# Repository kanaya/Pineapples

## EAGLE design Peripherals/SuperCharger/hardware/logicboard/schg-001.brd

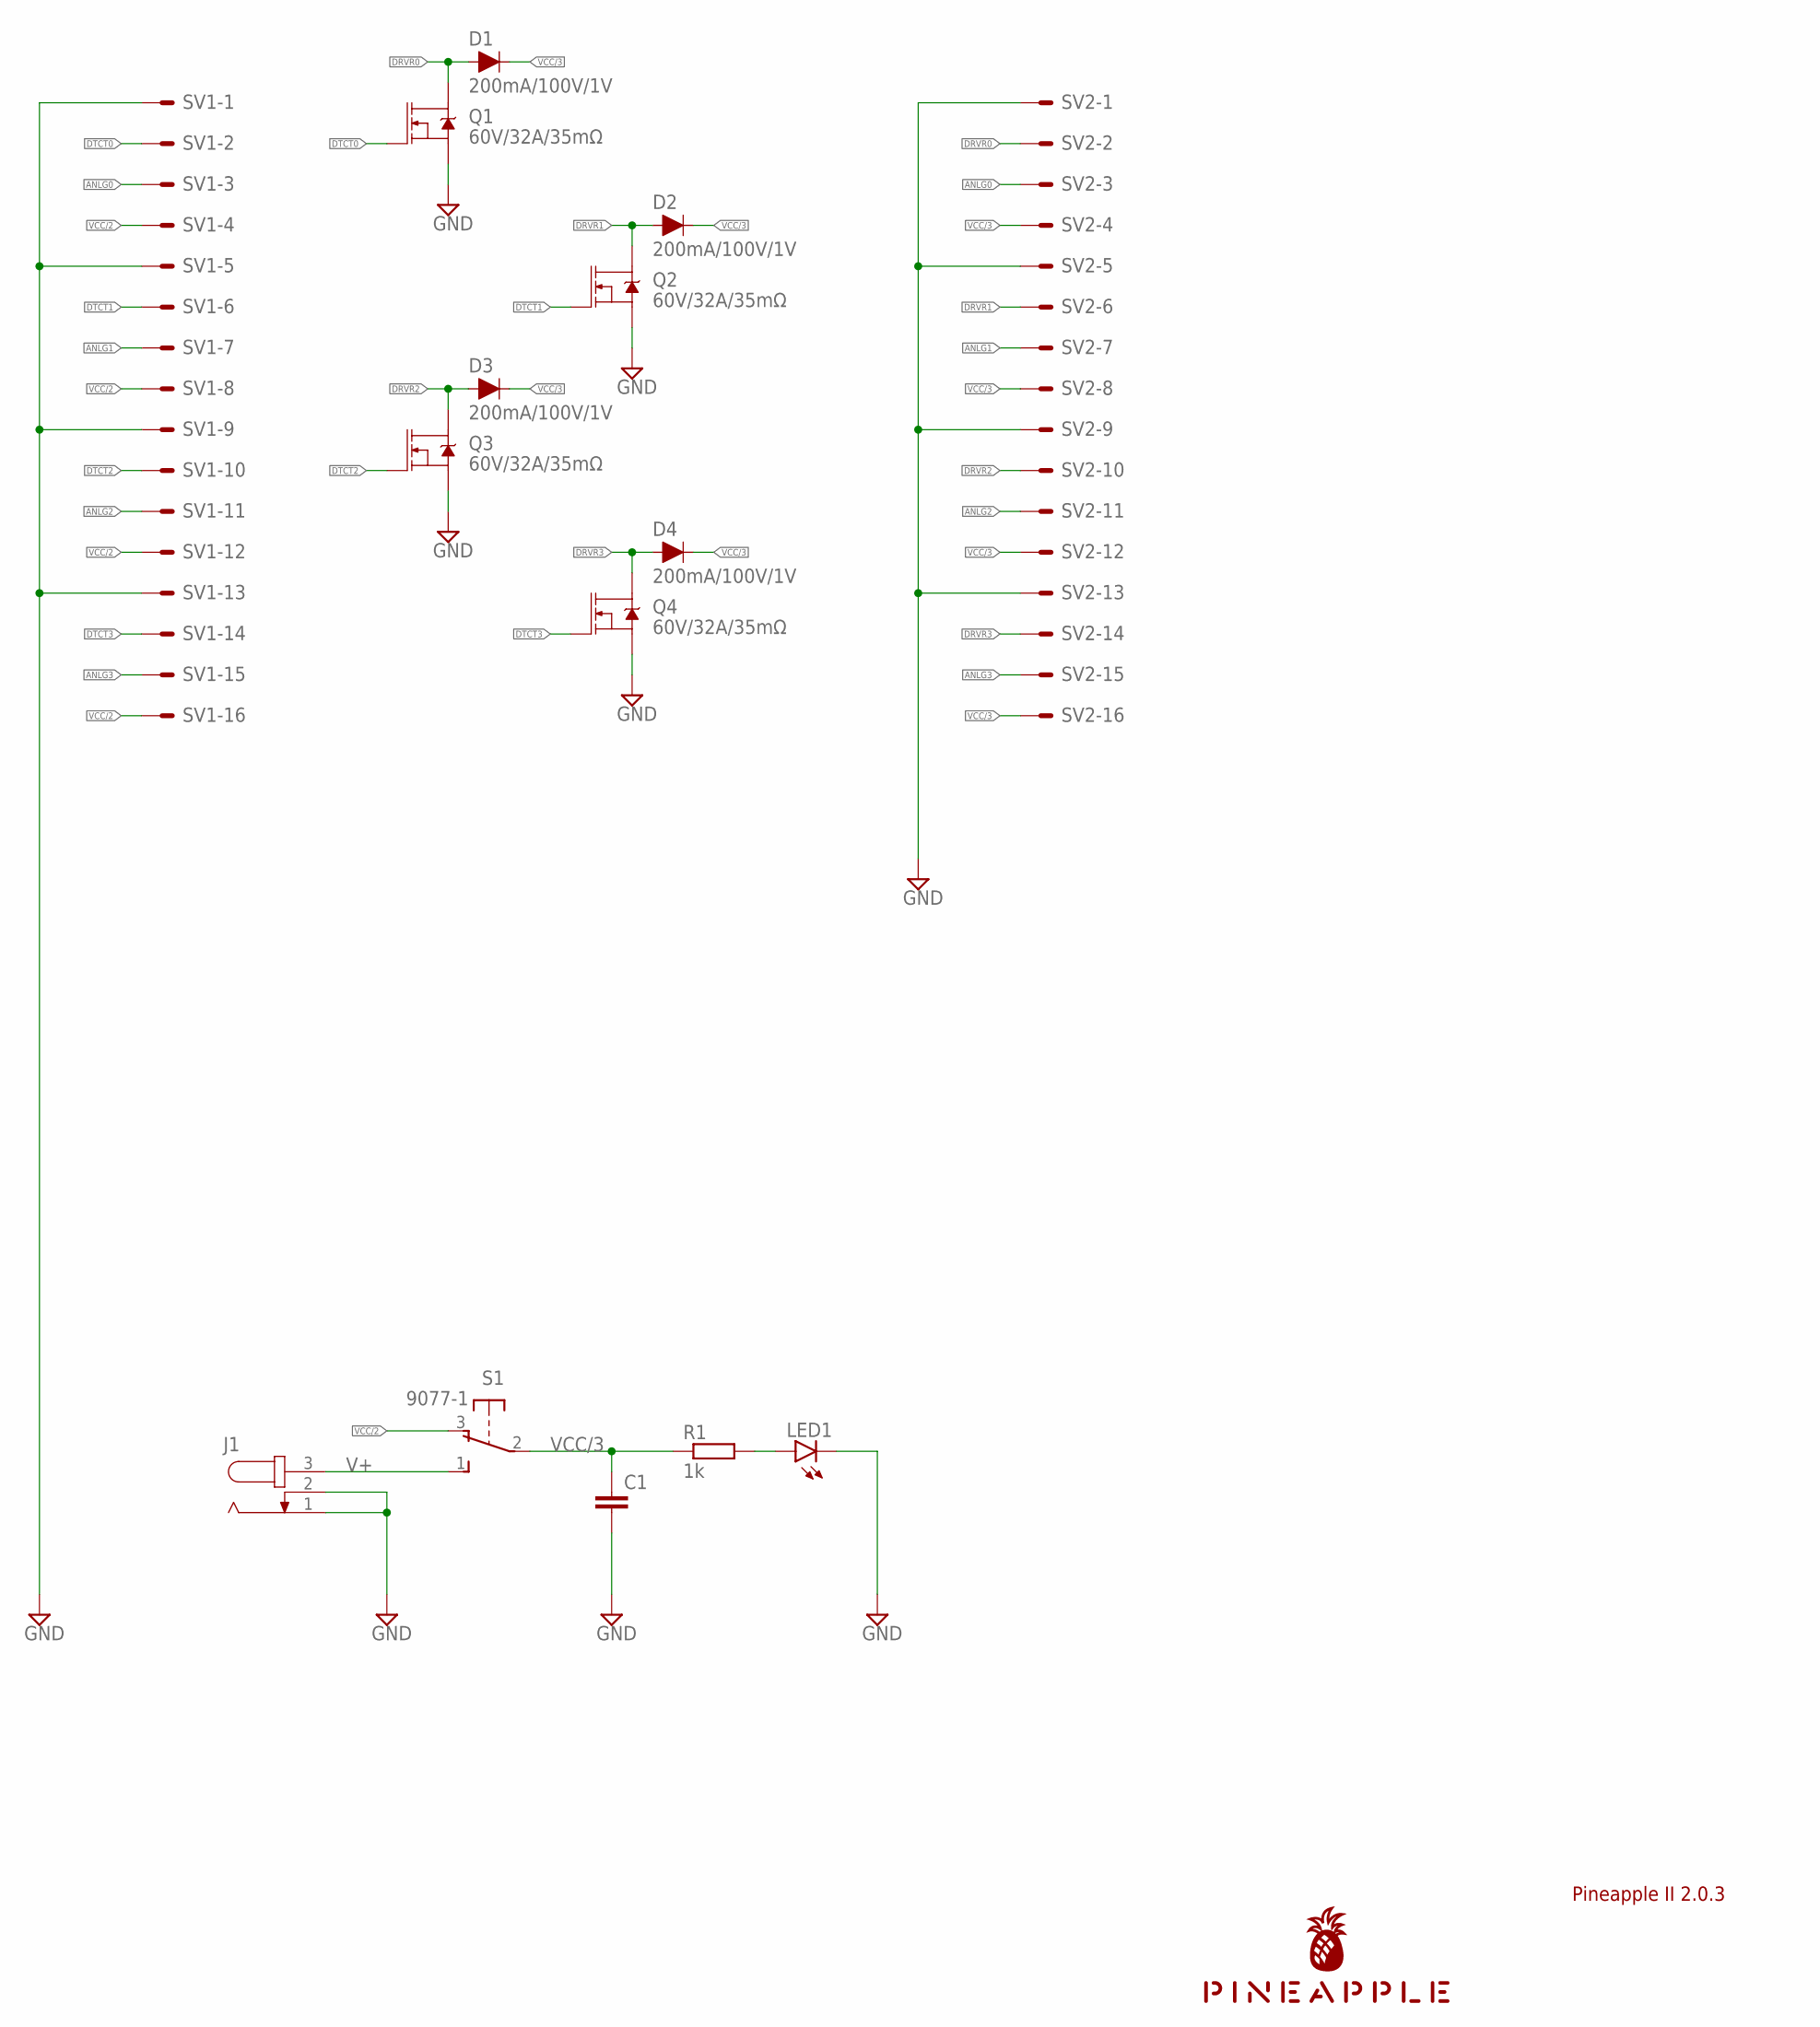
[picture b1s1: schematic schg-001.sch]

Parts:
C1: C-EU025-025X050; C025-025X050
D1, D2, D3, D4: 200mA/100V/1V; DIODE-1N4148
J1: JACK-PLUG0; SPC4077
LED1: LED3MM
Q1, Q2, Q3, Q4: 60V/32A/35mΩ; TO220V
R1: 1k; 0204/5
S1: 9077-1
SV1, SV2: ML16LE; ML16L
U$1: PINEAPPLE450_SILK

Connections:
ANLG0: SV1.3, SV2.3
ANLG1: SV1.7, SV2.7
ANLG2: SV1.11, SV2.11
ANLG3: SV1.15, SV2.15
DRVR0: D1.A, Q1.2 (D), SV2.2
DRVR1: D2.A, Q2.2 (D), SV2.6
DRVR2: D3.A, Q3.2 (D), SV2.10
DRVR3: D4.A, Q4.2 (D), SV2.14
DTCT0: Q1.1 (G), SV1.2
DTCT1: Q2.1 (G), SV1.6
DTCT2: Q3.1 (G), SV1.10
DTCT3: Q4.1 (G), SV1.14
GND: C1.2, J1.1, J1.2, LED1.K (C), Q1.3 (S), Q2.3 (S), Q3.3 (S), Q4.3 (S), SV1.1, SV1.5, SV1.9, SV1.13, SV2.1, SV2.5, SV2.9, SV2.13
V+: J1.3, S1.1 (S)
VCC2LED: LED1.A, R1.2
VCC/2: S1.3 (O), SV1.4, SV1.8, SV1.12, SV1.16
VCC/3: C1.1, D1.C, D2.C, D3.C, D4.C, R1.1, S1.2, SV2.4, SV2.8, SV2.12, SV2.16

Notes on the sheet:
Pineapple II 2.0.3

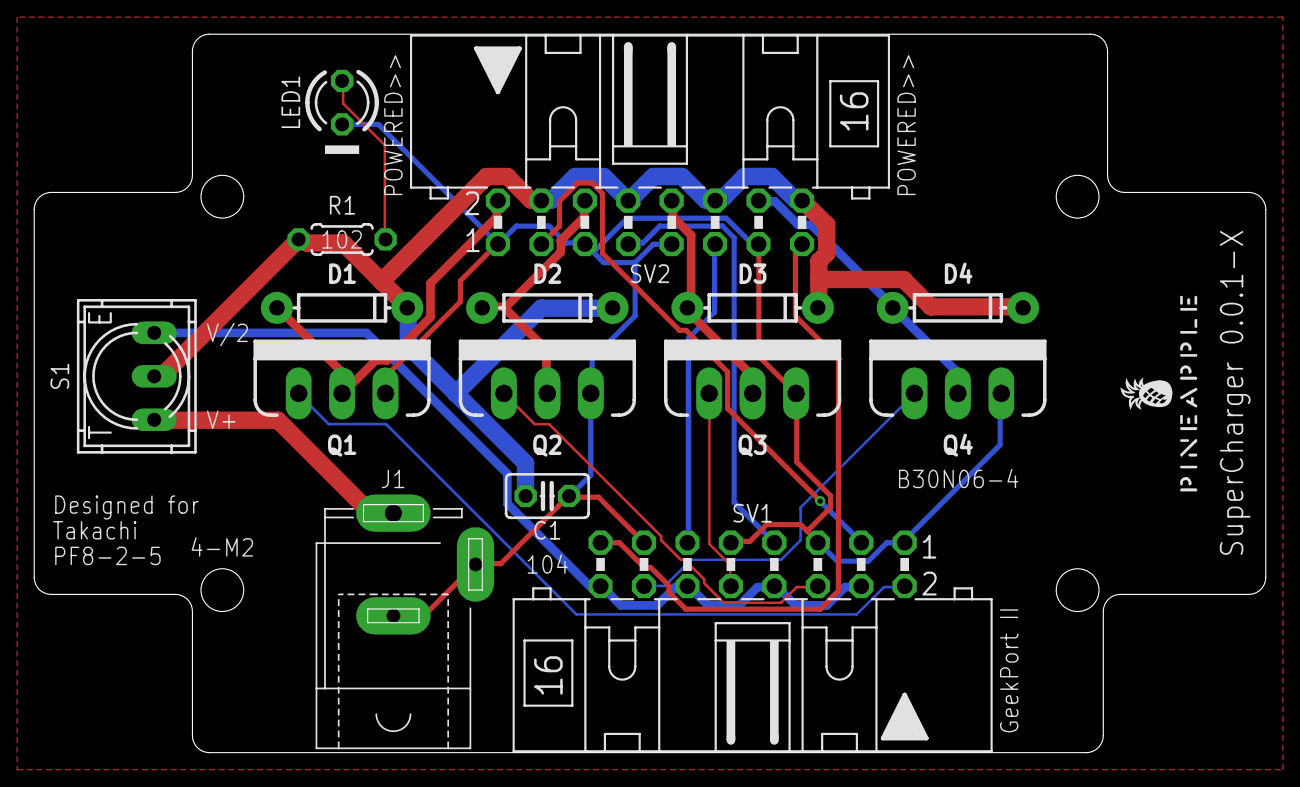
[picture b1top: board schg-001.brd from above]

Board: 2 copper layers, 72.0 x 42.0 mm, 16 parts (0 on the bottom side), 17 nets.

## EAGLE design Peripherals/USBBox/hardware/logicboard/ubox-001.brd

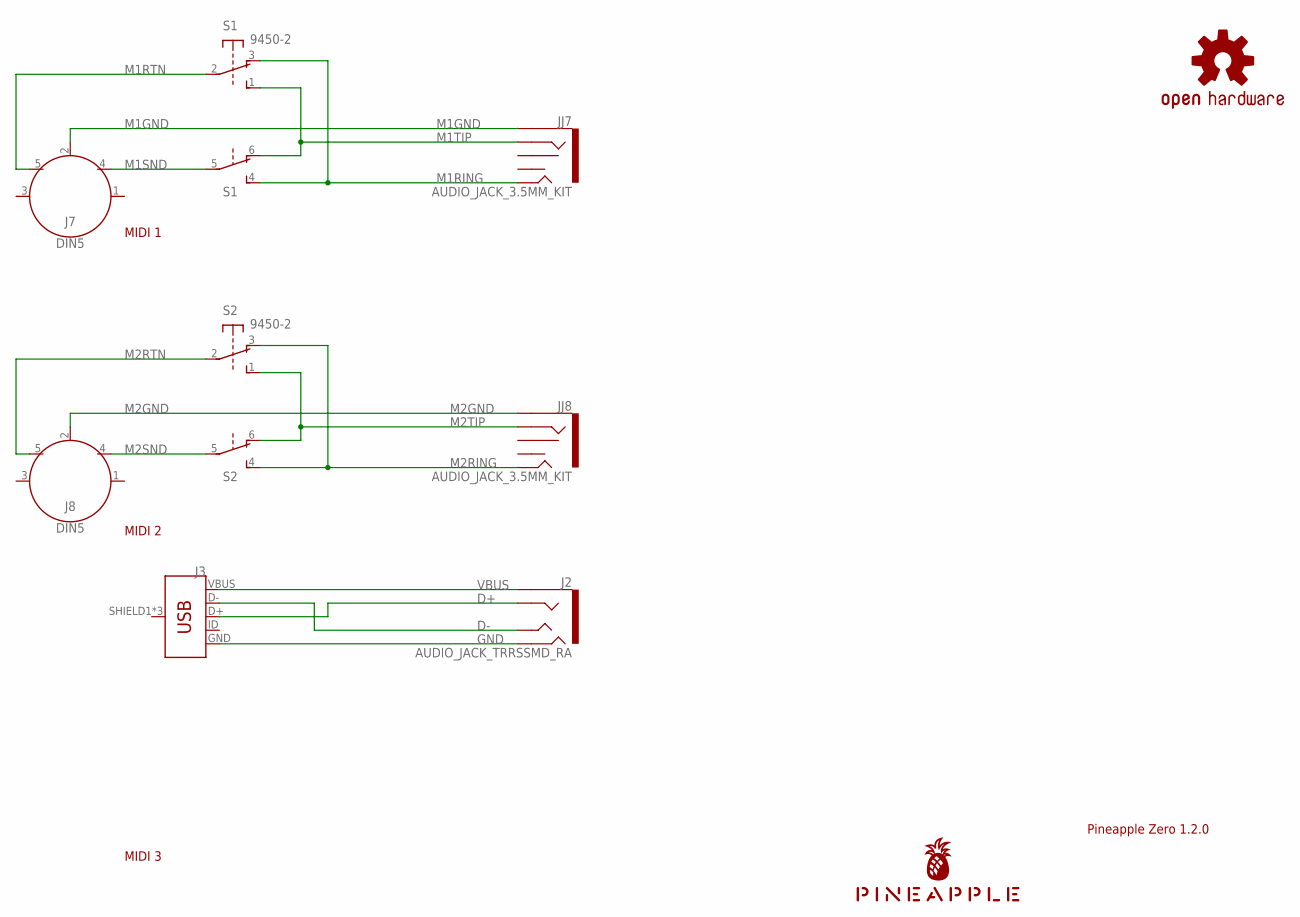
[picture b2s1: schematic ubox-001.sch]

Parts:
J2: AUDIO_JACK_TRRSSMD_RA; AUDIO_JACK_3.5MM_TRRS_SMD_RA
J3: USB_MICRO-BREDUCED_PASTE; USB-B-MICRO-SMD_RED_PASTE
J7, J8: DIN5; DIN5-RA-PTH
JJ7, JJ8: AUDIO_JACK_3.5MM_KIT; AUDIO-JACK-KIT
LOGO1: OSHW-LOGOS-COPPER; OSHW-LOGO-S_COPPER
S1, S2: 9450-2
U$1: PINEAPPLE450

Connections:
D+: J2.RING1, J3.D+
D-: J2.TIP, J3.D-
GND: J2.RING2, J3.GND
M1GND: J7.2, JJ7.SLEEVE
M1RING: JJ7.TIP, S1.3 (O), S1.4 (S)
M1RTN: J7.5, S1.2
M1SND: J7.4, S1.5
M1TIP: JJ7.RING, S1.1 (S), S1.6 (O)
M2GND: J8.2, JJ8.SLEEVE
M2RING: JJ8.TIP, S2.3 (O), S2.4 (S)
M2RTN: J8.5, S2.2
M2SND: J8.4, S2.5
M2TIP: JJ8.RING, S2.1 (S), S2.6 (O)
VBUS: J2.EARTH, J3.VBUS

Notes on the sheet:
Pineapple Zero 1.2.0
MIDI 1
MIDI 3
MIDI 2

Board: 2 copper layers, 10 parts (0 on the bottom side), 14 nets, no tracks yet.

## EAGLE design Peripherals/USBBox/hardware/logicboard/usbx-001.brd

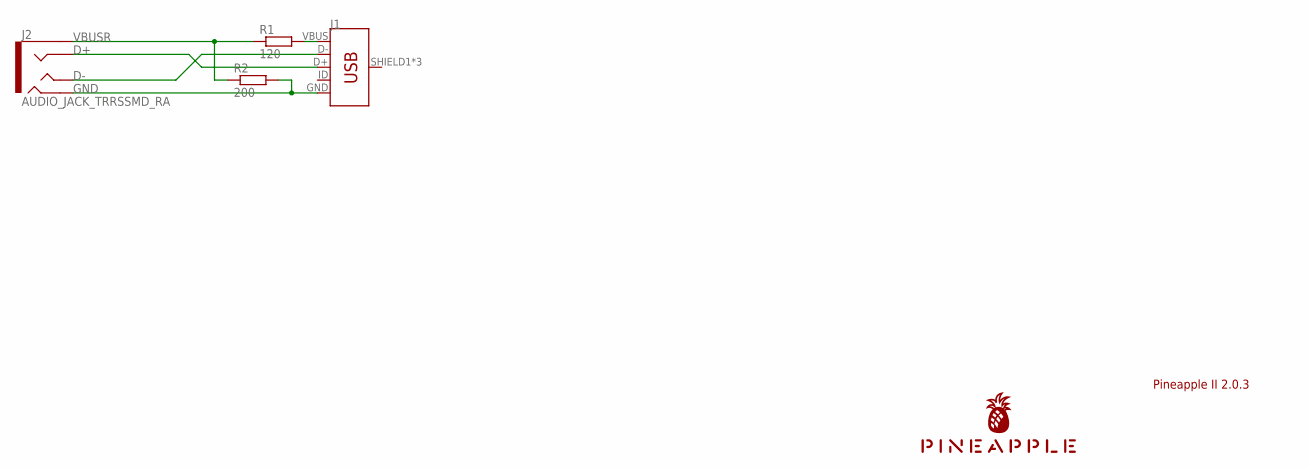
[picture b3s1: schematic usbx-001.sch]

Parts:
J1: USB_MICRO-B_FEMALE-SMT; USB-B-MICRO-SMD
J2: AUDIO_JACK_TRRSSMD_RA; AUDIO_JACK_3.5MM_TRRS_SMD_RA
R1: 120; R2012
R2: 200; R2012
U$1: PINEAPPLE450_SILK

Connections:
D+: J1.D+, J2.RING1
D-: J1.D-, J2.TIP
GND: J1.GND, J2.RING2, R2.2
VBUS: J1.VBUS, R1.2
VBUSR: J2.EARTH, R1.1, R2.1

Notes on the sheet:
Pineapple II 2.0.3

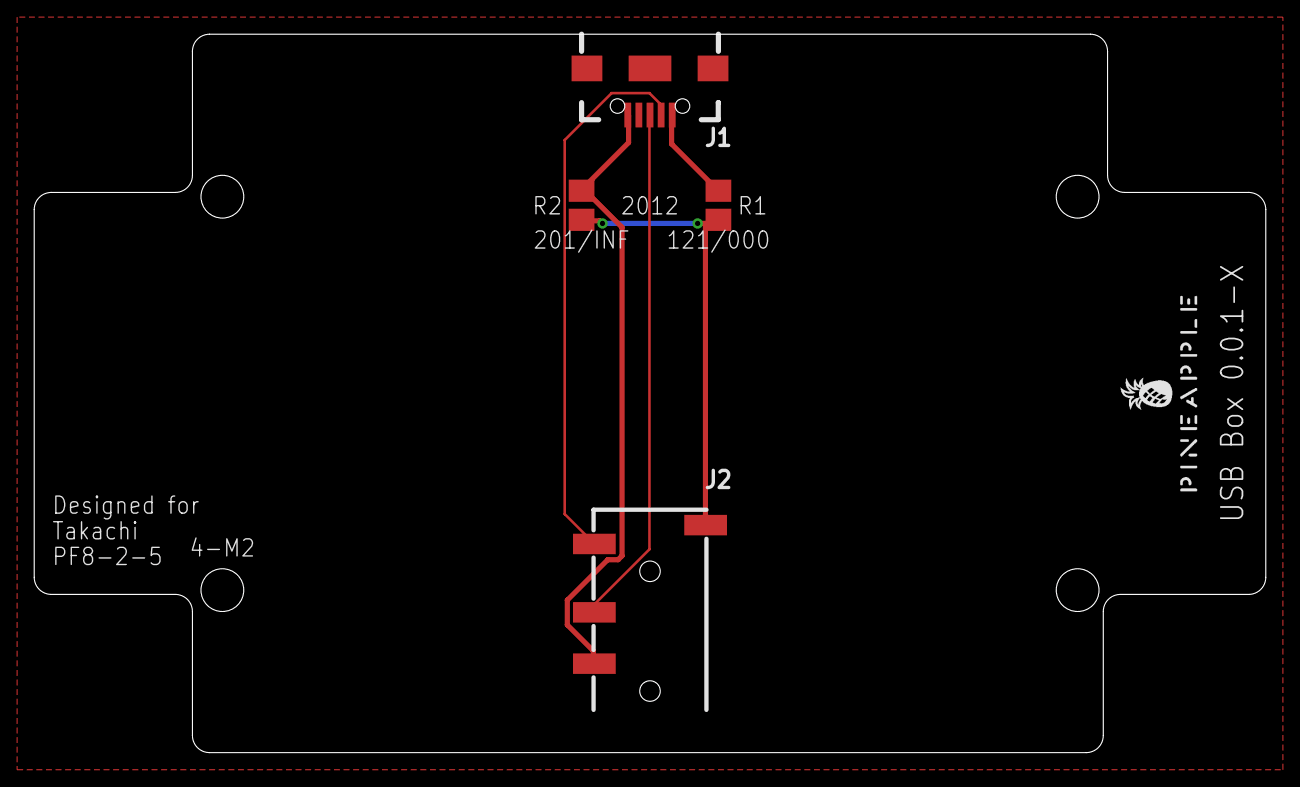
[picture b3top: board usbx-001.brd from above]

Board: 2 copper layers, 72.0 x 42.0 mm, 5 parts (0 on the bottom side), 5 nets.

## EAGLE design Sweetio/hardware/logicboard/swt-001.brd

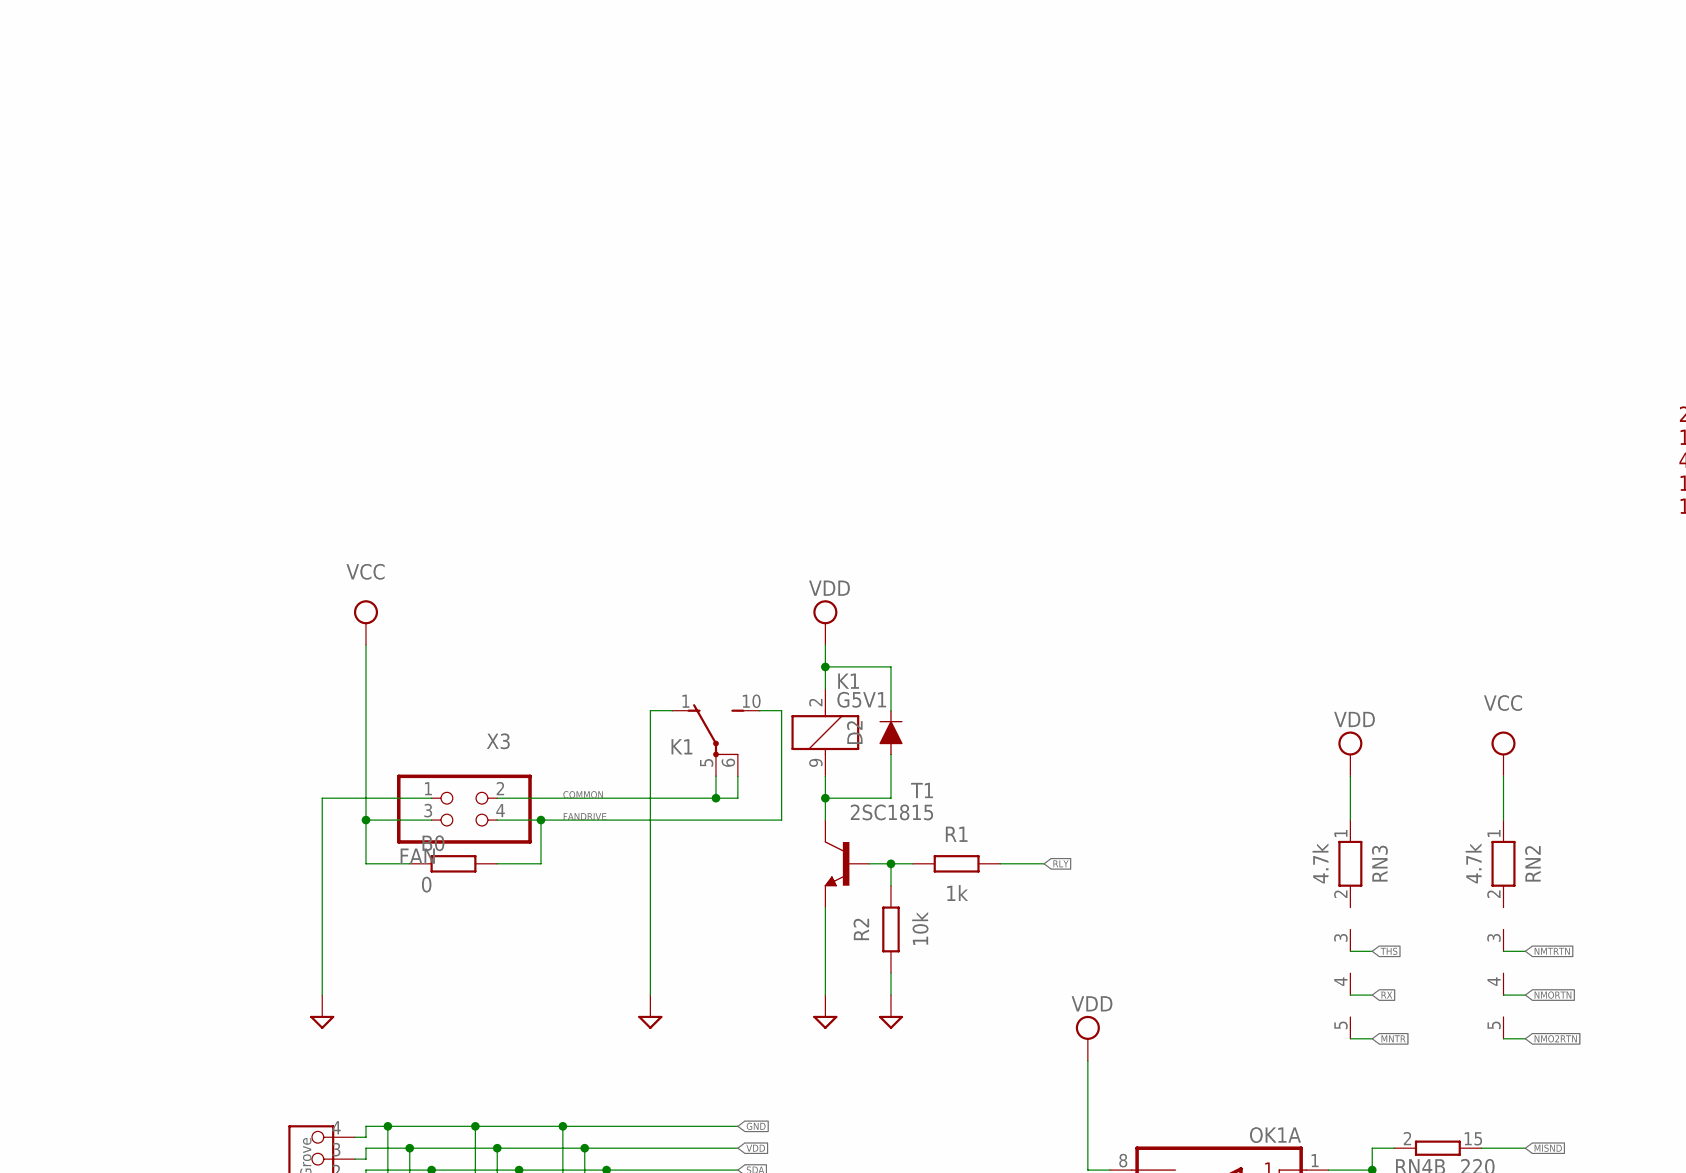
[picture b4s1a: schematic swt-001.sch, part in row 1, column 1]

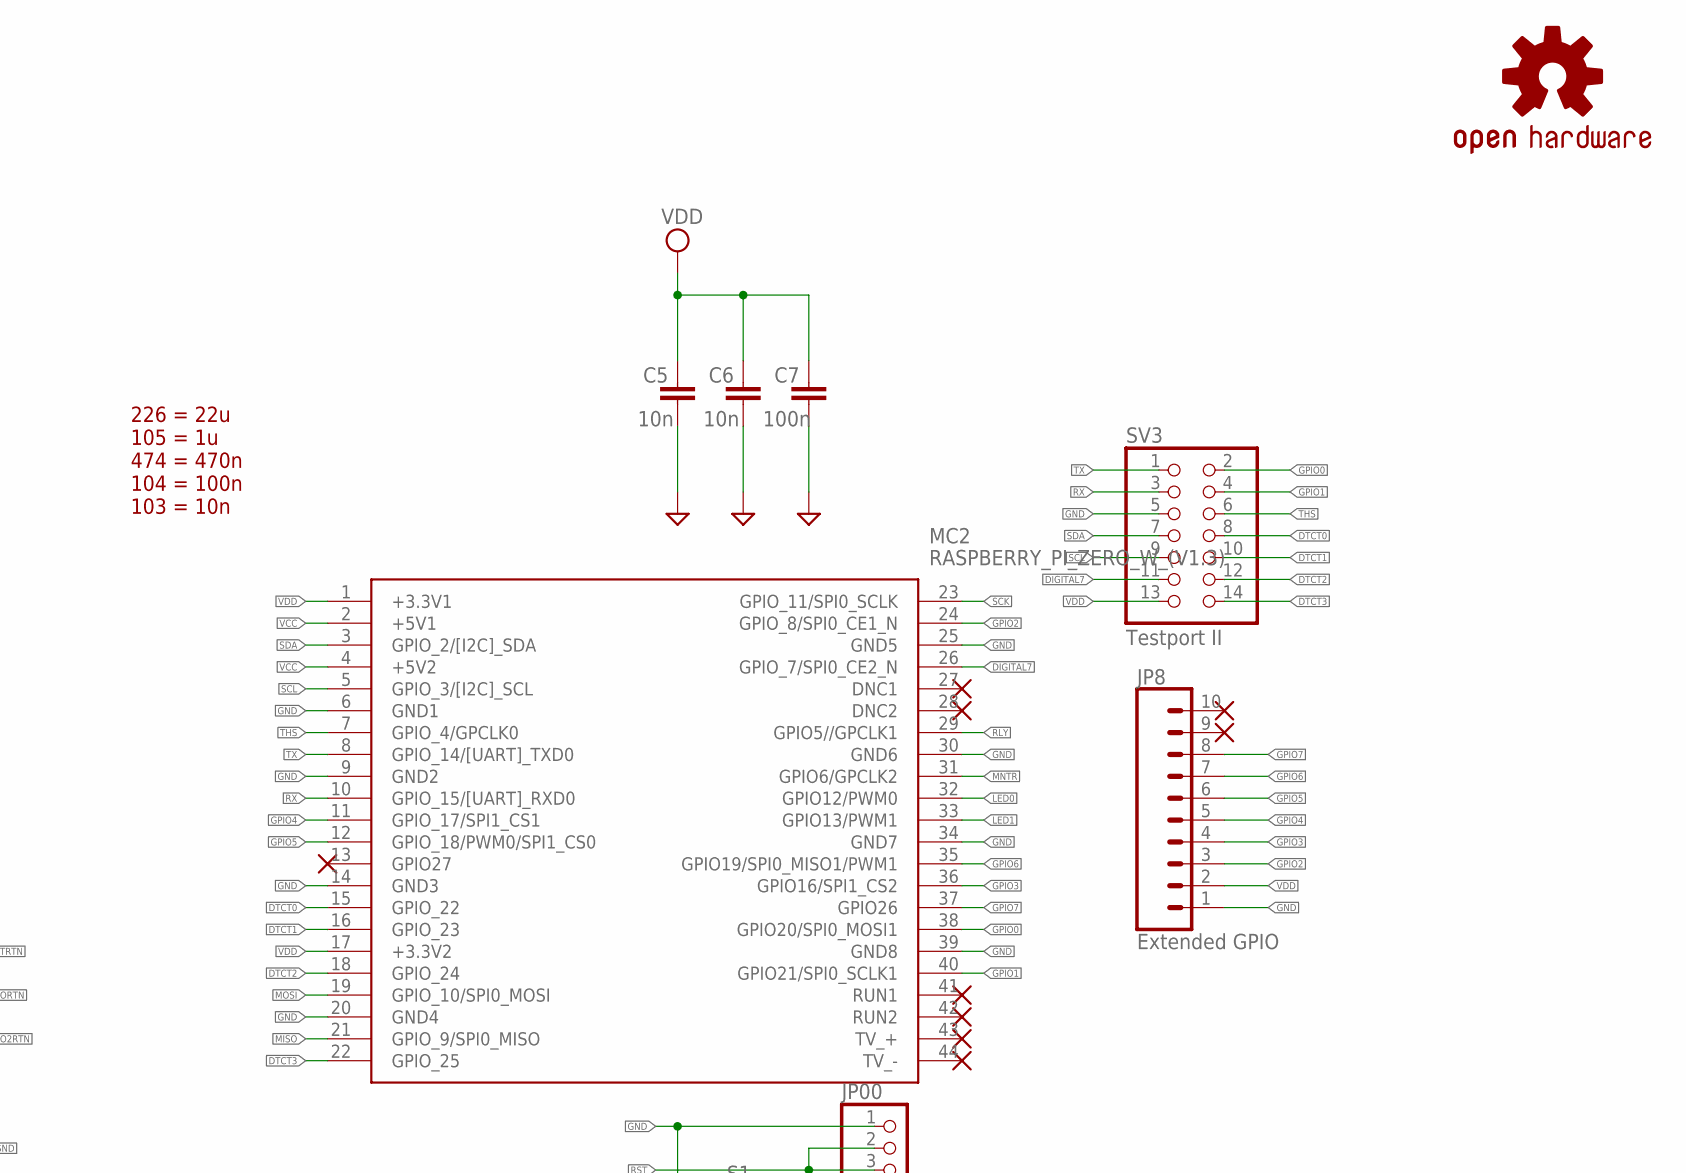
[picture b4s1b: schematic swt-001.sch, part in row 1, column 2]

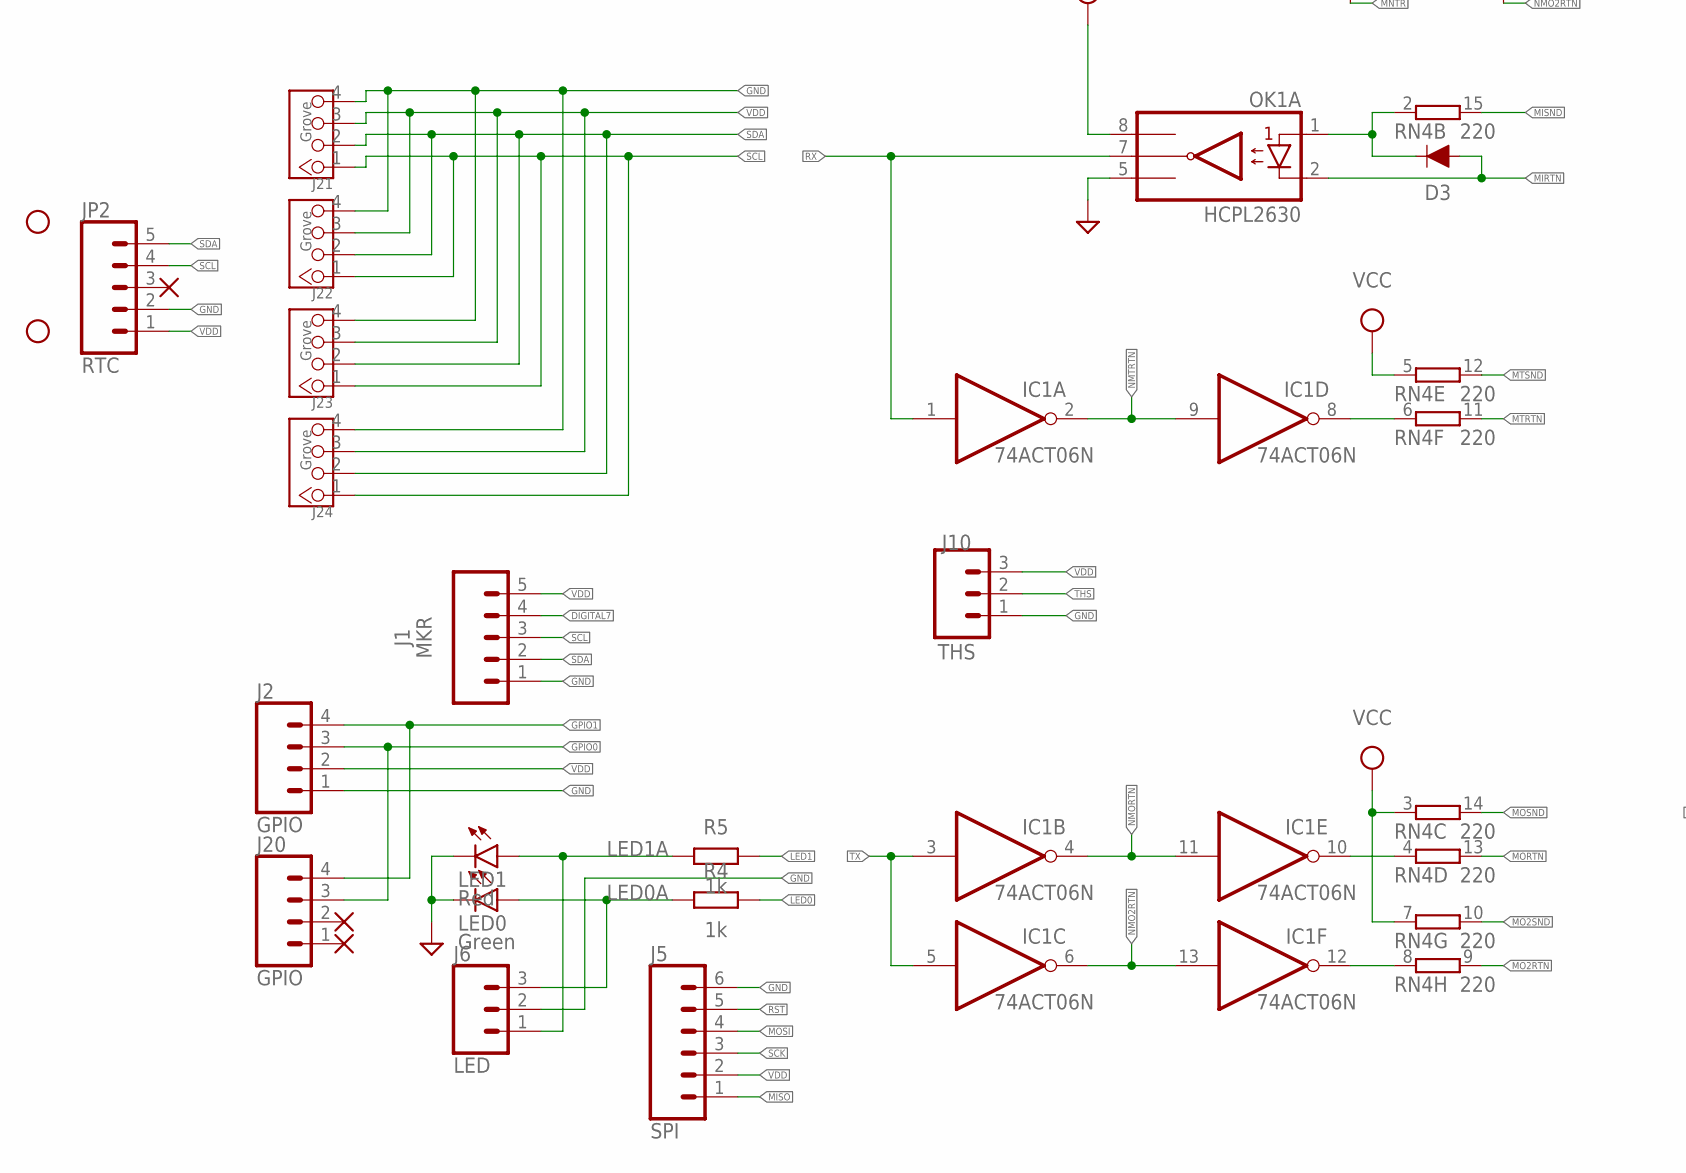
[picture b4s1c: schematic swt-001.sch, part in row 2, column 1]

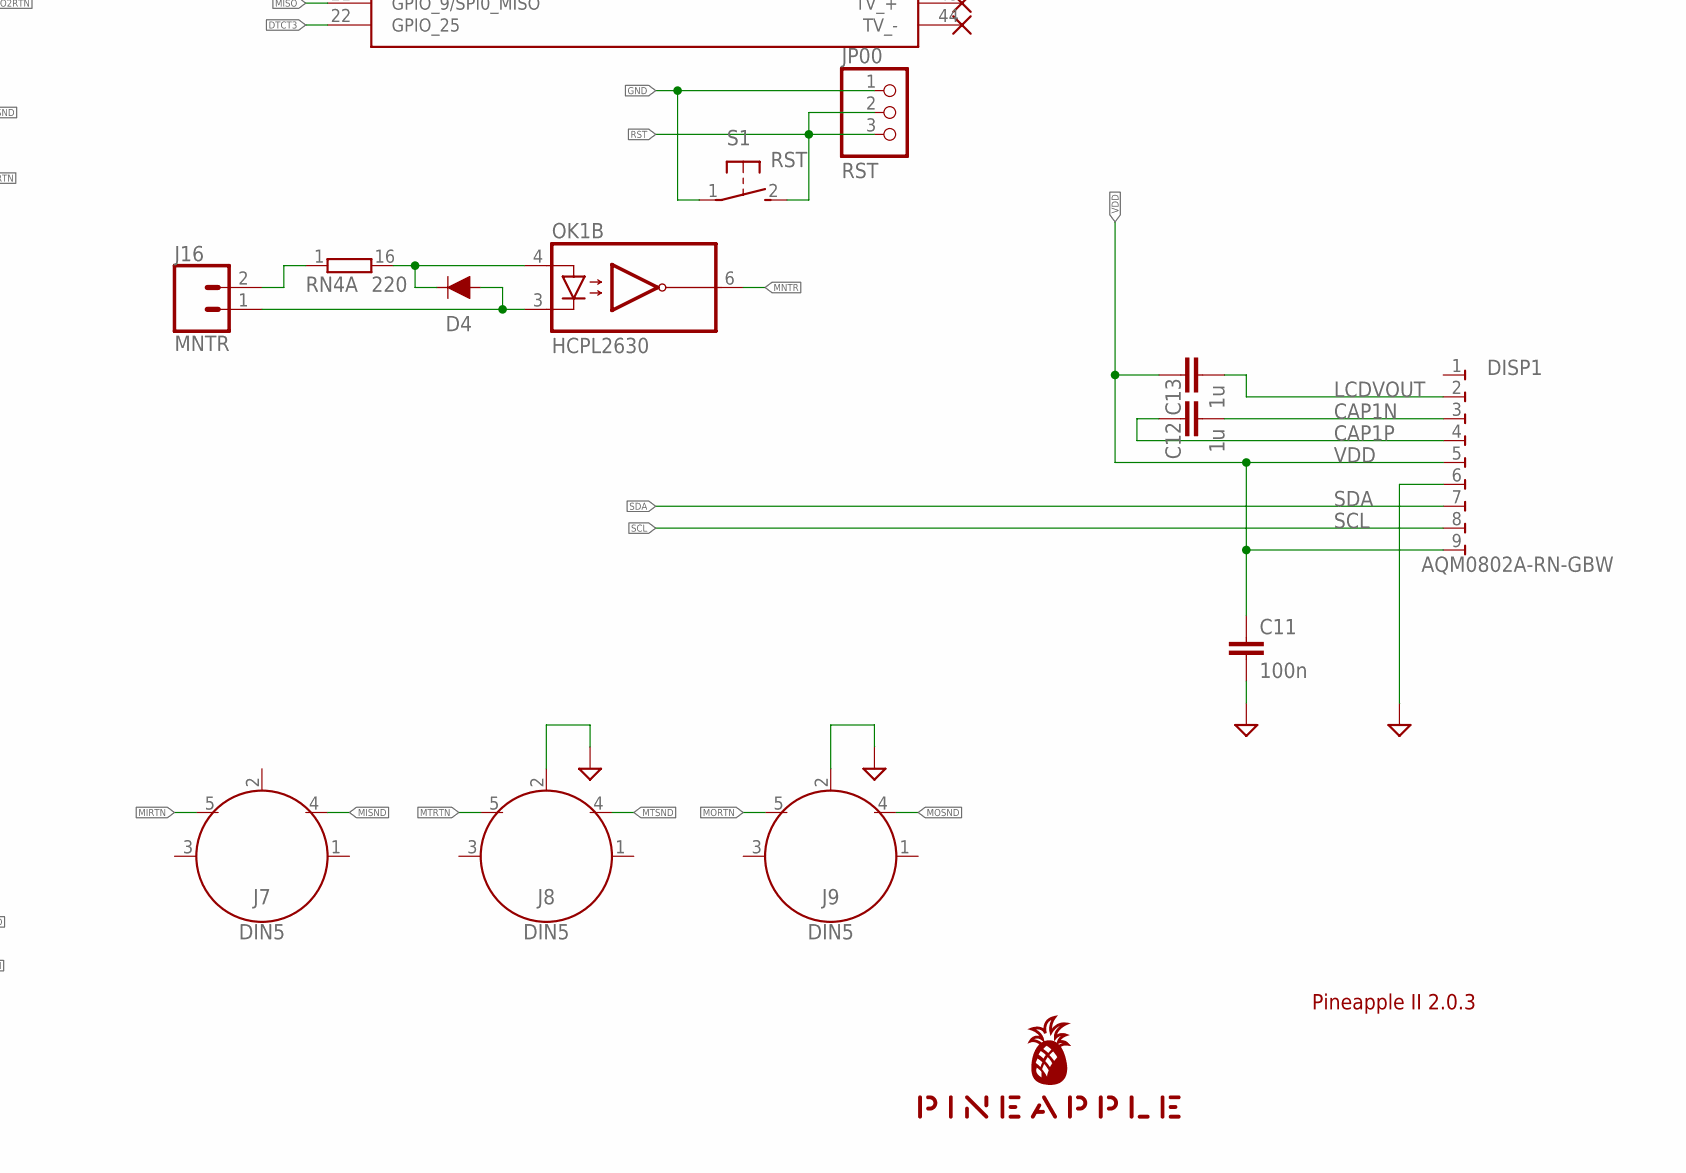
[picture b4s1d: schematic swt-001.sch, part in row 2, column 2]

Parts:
B0: 0; M3216
C5, C6: 10n; C025-024X044
C7, C11: 100n; C025-024X044
C12, C13: 1u; C050-024X044
D2, D3, D4: DIODE-1N4148
DISP1: AQM0802A-RN-GBW; AQM0802A-RN-GBW-FOOTPRINT
H1, H2: STAND-OFF
IC1: 74ACT06N; DIL14
J1: MKR; JST-5-PTH
J2: GPIO; JST-4-PTH
J5: SPI; 1X06_1.27MM
J6: LED; JST-3-PTH-VERT
J7, J8, J9: DIN5; DIN5-RA-PTH
J10: THS; JST-3-PTH-VERT
J16: MNTR; JST-2-PTH-NS
J20: GPIO; 1X04_1.27MM
J21, J22: Grove; 4P-2.0-90D
J23, J24: Grove; 4P-2.0-W/O-BUCKLE
JP00: RST; 1X03
JP2: RTC; 1X05
JP8: Extended GPIO; 1X10_LOCK
K1: G5V1
LED0: Green; KA-3528ASYC
LED1: Red; KA-3528ASYC
LOGO1: OSHW-LOGOS-COPPER; OSHW-LOGO-S_COPPER
MC2: RASPBERRY_PI_ZERO_W_(V1.3); RASPBERRYPIZEROWV13
OK1: HCPL2630; DIL08
R1, R4, R5: 1k; 0204/5
R2: 10k; 0204/5
RN2, RN3: 4.7k; RN-5
RN4: 220; DIL16
S1: RST; B3F-31XX
SV3: Testport II; 2X07
T1: 2SC1815; TO92-ECB
U$1: PINEAPPLE450_SILK
X3: FAN; 2X02

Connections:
BASE: R1.1, R2.2, T1.B
CAP1N: C12.2, DISP1.3
CAP1P: C12.1, DISP1.4
COLLECTOR: D2.A, K1.9 (2), T1.C
COMMON: K1.5, K1.6, X3.2
DIGITAL7: J1.4, MC2.26 (GPIO_7/SPI0_CE2_N), SV3.11
DTCT0: MC2.15 (GPIO_22), SV3.8
DTCT1: MC2.16 (GPIO_23), SV3.10
DTCT2: MC2.18 (GPIO_24), SV3.12
DTCT3: MC2.22 (GPIO_25), SV3.14
FANDRIVE: B0.2, K1.10 (S), X3.4
GND: C5.2, C6.2, C7.2, C11.2, DISP1.6, IC1.7 (GND), J1.1, J2.1, J5.6, J6.2, J8.2, J9.2, J10.1, J21.4, J22.4, J23.4, J24.4, JP00.1, JP2.2, JP8.1, K1.1 (O), LED0.C, LED1.C, MC2.6 (GND1), MC2.9 (GND2), MC2.14 (GND3), MC2.20 (GND4), MC2.25 (GND5), MC2.30 (GND6), MC2.34 (GND7), MC2.39 (GND8), OK1.5 (GND), R2.1, S1.1, SV3.5, T1.E, X3.1
GPIO0: J2.3, J20.3, MC2.38 (GPIO20/SPI0_MOSI1), SV3.2
GPIO1: J2.4, J20.4, MC2.40 (GPIO21/SPI0_SCLK1), SV3.4
GPIO2: JP8.3, MC2.24 (GPIO_8/SPI0_CE1_N)
GPIO3: JP8.4, MC2.36 (GPIO16/SPI1_CS2)
GPIO4: JP8.5, MC2.11 (GPIO_17/SPI1_CS1)
GPIO5: JP8.6, MC2.12 (GPIO_18/PWM0/SPI1_CS0)
GPIO6: JP8.7, MC2.35 (GPIO19/SPI0_MISO1/PWM1)
GPIO7: JP8.8, MC2.37 (GPIO26)
LCDVOUT: C13.2, DISP1.2
LED0: MC2.32 (GPIO12/PWM0), R4.2
LED0A: J6.3, LED0.A, R4.1
LED1: MC2.33 (GPIO13/PWM1), R5.2
LED1A: J6.1, LED1.A, R5.1
MIDIINSND: D3.C, OK1.1 (A1), RN4.2 (1)
MIRTN: D3.A, J7.5, OK1.2 (C1)
MISND: J7.4, RN4.15 (2)
MISO: J5.1, MC2.21 (GPIO_9/SPI0_MISO)
MNTR: MC2.31 (GPIO6/GPCLK2), OK1.6 (VO2), RN3.5
MNTRA: J16.2, RN4.1
MNTRAA: D4.C, OK1.4 (A2), RN4.16 (2)
MNTRK: D4.A, J16.1, OK1.3 (C2)
MO2RTN: RN4.9 (2)
MO2RTNRAW: IC1.12 (O), RN4.8 (1)
MO2SND: RN4.10 (2)
MORTN: J9.5, RN4.13 (2)
MORTNRAW: IC1.10 (O), RN4.4 (1)
MOSI: J5.4, MC2.19 (GPIO_10/SPI0_MOSI)
MOSND: J9.4, RN4.14 (2)
MTRTN: J8.5, RN4.11 (2)
MTRTNRAW: IC1.8 (O), RN4.6 (1)
MTSND: J8.4, RN4.12 (2)
NMO2RTN: IC1.6 (O), IC1.13 (I), RN2.5
NMORTN: IC1.4 (O), IC1.11 (I), RN2.4
NMTRTN: IC1.2 (O), IC1.9 (I), RN2.3
RLY: MC2.29 (GPIO5//GPCLK1), R1.2
RST: J5.5, JP00.2, JP00.3, S1.2 (S)
RX: IC1.1 (I), MC2.10 (GPIO_15/[UART]_RXD0), OK1.7 (VO1), RN3.4, SV3.3
SCK: J5.3, MC2.23 (GPIO_11/SPI0_SCLK)
SCL: DISP1.8, J1.3, J21.1, J22.1, J23.1, J24.1, JP2.4, MC2.5 (GPIO_3/[I2C]_SCL), SV3.9
SDA: DISP1.7, J1.2, J21.2, J22.2, J23.2, J24.2, JP2.5, MC2.3 (GPIO_2/[I2C]_SDA), SV3.7
THS: J10.2, MC2.7 (GPIO_4/GPCLK0), RN3.3, SV3.6
TX: IC1.3 (I), IC1.5 (I), MC2.8 (GPIO_14/[UART]_TXD0), SV3.1
VCC: B0.1, IC1.14 (VCC), MC2.2 (+5V1), MC2.4 (+5V2), RN2.1, RN4.3 (1), RN4.5 (1), RN4.7 (1), X3.3
VDD: C5.1, C6.1, C7.1, C11.1, C13.1, D2.C, DISP1.5, DISP1.9, J1.5, J2.2, J5.2, J10.3, J21.3, J22.3, J23.3, J24.3, JP2.1, JP8.2, K1.2 (1), MC2.1 (+3.3V1), MC2.17 (+3.3V2), OK1.8 (VCC), RN3.1, SV3.13

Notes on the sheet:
Pineapple II 2.0.3
226 = 22u 105 = 1u 474 = 470n 104 = 100n 103 = 10n

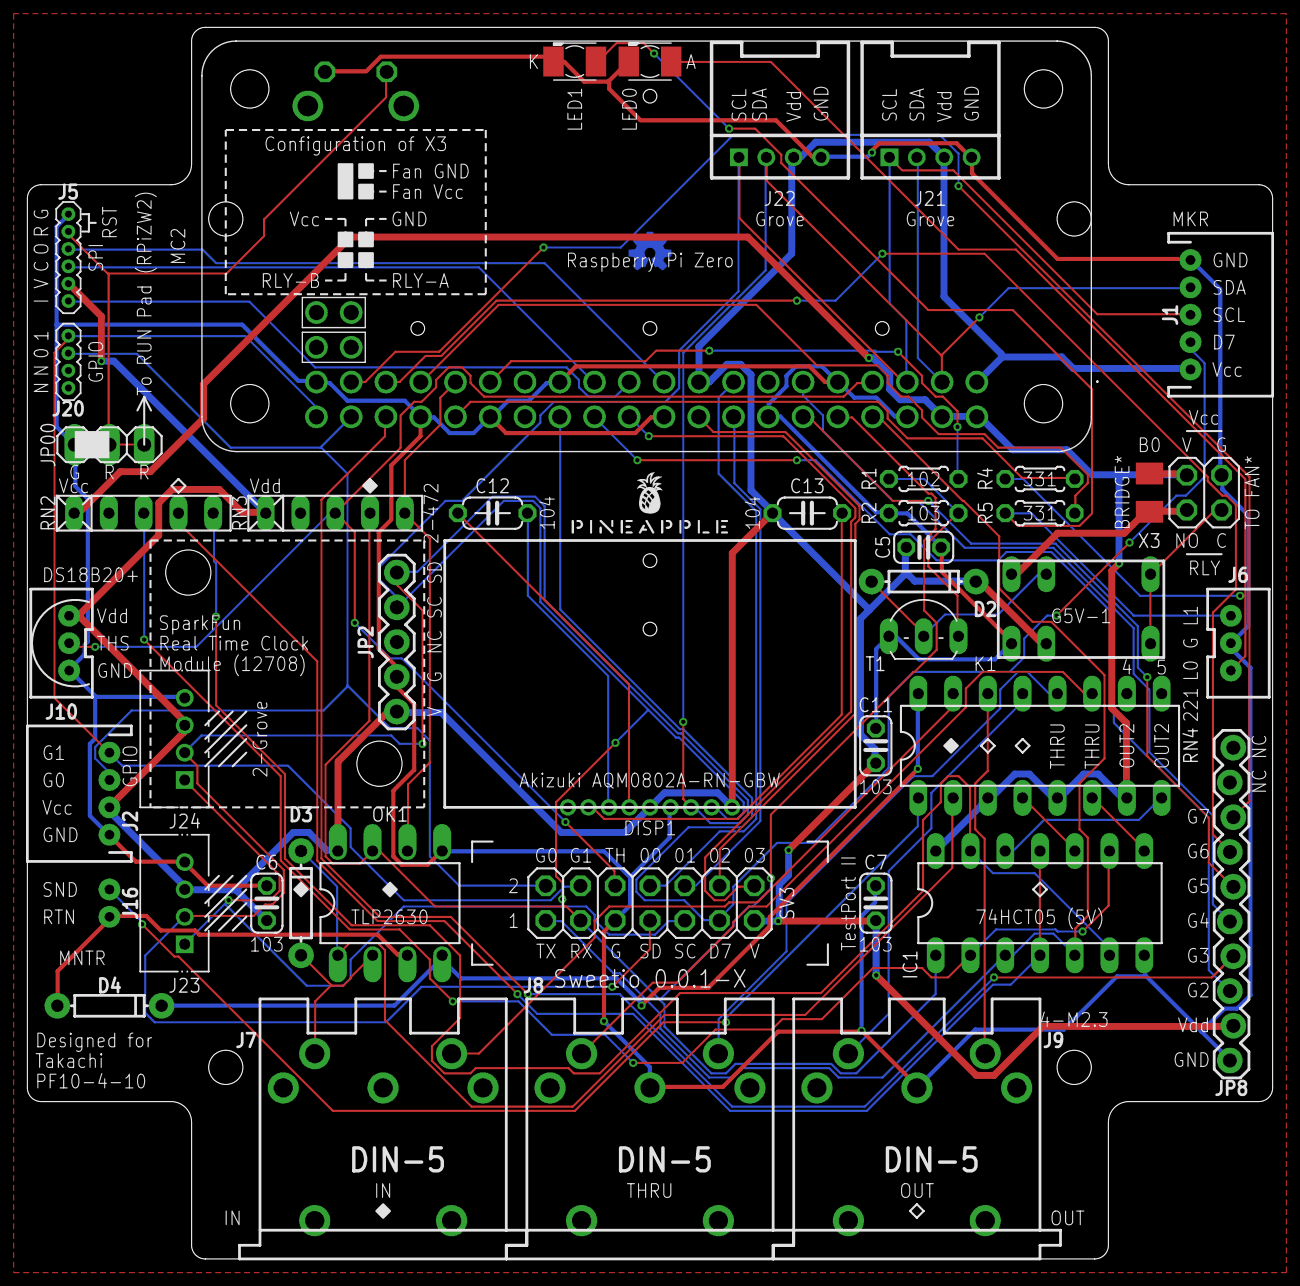
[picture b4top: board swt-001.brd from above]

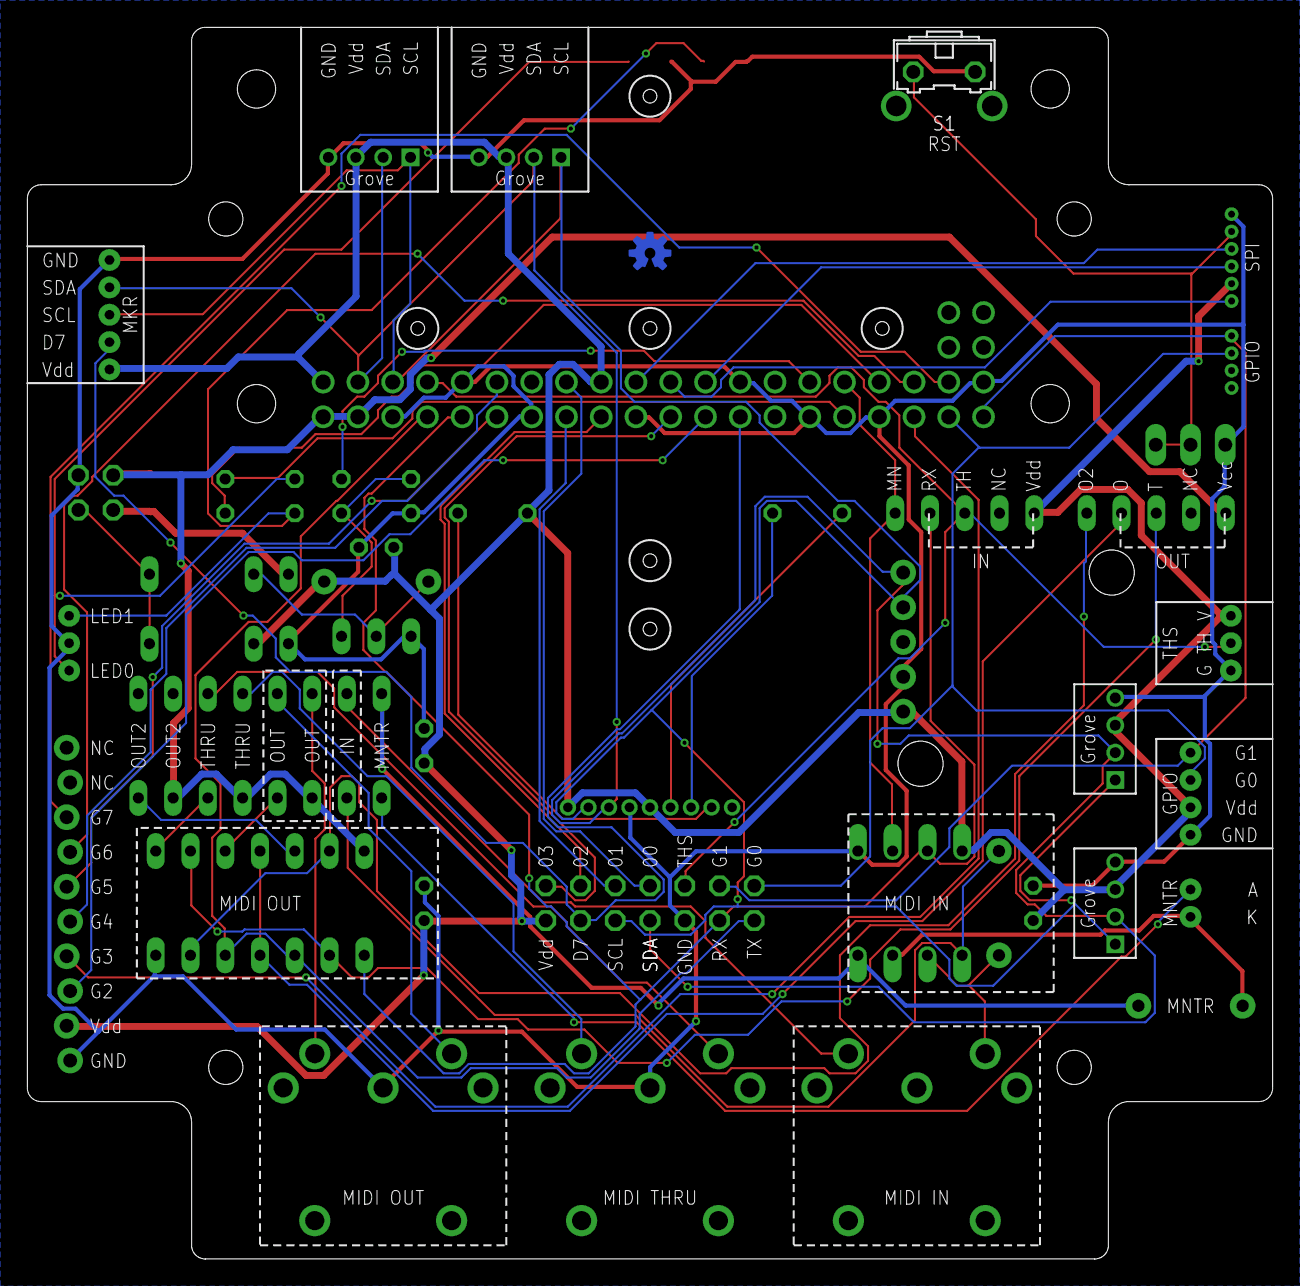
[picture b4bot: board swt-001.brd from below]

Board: 2 copper layers, 91.0 x 90.0 mm, 49 parts (2 on the bottom side), 54 nets.

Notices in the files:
parts and their libraries:
SparkFun-DiscreteSemi: Licensing: Creative Commons ShareAlike 4.0 International - https://creativecommons.org/licenses/by-sa/4.0
